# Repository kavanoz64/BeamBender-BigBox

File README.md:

# BeamBender BigBox

A digital scandoubler and HDMI output card for the **Amiga 4000**, with the **Amiga 2000 and 3000** supported as well.

The card plugs into the video slot, taps the digital RGB signals before they ever reach a DAC, and outputs clean **HDMI** with audio. No analog stage, no capture artifacts, no flicker.

> This project is a big-box adaptation of [**jbilander/BeamBender**](https://github.com/jbilander/BeamBender), Jörgen Bilander's scandoubler for the Amiga 1200 (and 500). The original design's approach and much of its analog and HDMI circuitry carry over directly. Jörgen has also provided hardware guidance throughout this redesign. All credit for the concept belongs upstream.

**Status: revision 0.3 works on the Amiga 4000D, 4000T, 3000 and 2000 (OCS, ECS and AGA): every Amiga screen mode including the A2024, DCTV and HAM-E pictures, motion-adaptive deinterlacing, integer and half-step scaling, and fourteen output formats from 640x480 to 1920x1200.** See [Status](#status).

**Using the card:** the [User Guide](USER_GUIDE.md) explains the on-screen menu and the three buttons. Loading the firmware is in [`Firmware/`](Firmware/README.md), the Amiga tools in [`BBLink/`](BBLink/README.md).

---

## What's different from the A1200 original

The A1200 version clips onto the Lisa chip and connects to the main board with an FFC cable. Big-box Amigas have the same signals on the video slot, so this version is a **single PCB with no cables**, taking digital RGB, syncs, the pixel clock, audio and power straight off the slot.

| | A1200 BeamBender | BeamBender BigBox |
|---|---|---|
| Signal source | Lisa chip (PLCC-84 clip) | Video slot |
| Boards | Two, joined by FFC | One |
| FPGA | Gowin GW1NR-9 (on-board) | Colorlight i5 or i9 module (SO-DIMM socket) |
| Video RAM | FPGA-internal | 8 MB 32-bit SDRAM on module |
| Audio in | 3.5 mm jack | Video slot, plus aux header and jack, mixed |
| Power | External connector | Slot |

---

## Hardware

**FPGA:** a [Colorlight i5 v7.0](https://github.com/wuxx/Colorlight-FPGA-Projects) module in a 200-pin DDR2 SO-DIMM socket (TE 1473149-4), with a Lattice **ECP5 LFE5U-25F** (24k LUT), **8 MB of 32-bit SDRAM** for the frame buffer, and its own configuration flash and regulators. The ECP5 only comes in BGA, so the module is deliberate: a dead one is a socket swap, not a rework job. **SO-DIMM pin 41**, the one ball that differs between the i5 and the i9, is left unconnected so the two are interchangeable.

**The i9 (LFE5U-45F, 44k LUT, 4 PLLs) is the recommended module** for the Rev 0.3 board. It drops into the same socket, and on a board without the clock generator below its two extra PLLs clock the seven formats that need 40, 65, 108 or 162 MHz. It is also the module with room for what comes next. Build with an i9 unless cost decides.

The **i5 (LFE5U-25F)** is the cheaper option, with its own bitstream. On its own it runs the other seven formats (640x480, 720x576 / 720x480, 1280x720, 1280x800, 1680x1050, 1920x1080 and 1920x1200), enough for most televisions and monitors; with the **Si5351C** fitted it runs all fourteen. It will be the recommended module for the Rev 0.4 and later boards.

**Clock generator:** an **Si5351C** makes the pixel clocks the ECP5's PLLs cannot make from 27 MHz: 162 MHz for 1600x1200, 108 for 1280x960, 1280x1024, 1440x900 and 1600x900, 65 for 1024x768 and 40 for 800x600. It is a rework on revision 0.3 and part of the next revision. One firmware per module serves boards with and without it: the card measures its clocks at power-up and offers only the formats it can make.

**Video out:** an **SiI9022A** HDMI transmitter, fed 24-bit RGB at up to 162 MHz. An ECP5 without SERDES cannot generate HDMI's TMDS signals itself fast enough for 1080p60.

**Audio:** an **AK5720** 24-bit ADC sends I²S straight to the SiI9022A. Ahead of it, an **OPA1692** summing amplifier mixes the Amiga's audio from the slot with an auxiliary input, on an internal header or a 3.5 mm jack (a plug in the jack disconnects the header), so another card's audio or an external source can be folded in.

**HDMI +5V:** a **TPS2553** load switch feeds HDMI pin 18, current-limited and blocking reverse current, so neither a shorted cable nor a television pushing 5V back can reach the Amiga's supply. The on-screen display reports its fault line.

**Level shifting:** two 74LVC16244 buffers translate the Amiga's 5V logic to 3.3V; the ECP5 is *not* 5V tolerant.

**Board:** 157.5 x 90 mm, 4-layer, with dedicated ground and 3V3 planes.

### Where to buy the module

[Colorlight i5 + ext-board bundle on AliExpress](https://www.aliexpress.us/item/3256807602160285.html)

Buy the **module and the dev board together**. The card programs the module in place through its JTAG header, but the dev board is a second, independent way to load or recover a bitstream.

---

## Clock architecture

| Clock | Source | ECP5 pin | PLL |
|---|---|---|---|
| **C28O**, 28.375 MHz PAL / 28.636 NTSC | Alice, via slot | 91 · `PCLKT2_1` | none, already the pixel clock |
| **VCDAC x2**, 14.19 MHz | Agnus/Alice CDAC, doubled on-board | 81 · `PCLKT3_1` | x2 to 28.375 MHz |
| **27 MHz** | on-board oscillator | 134 · `PCLKT7_1` | x5.5 to 148.5 MHz output |
| **24.576 MHz** | on-board oscillator | 89 · `PCLKT2_0` | none, audio MCLK reference |

**27 MHz** because 148.5 MHz, the pixel clock of 1080p at both 50 and 60 Hz, is exactly 27 x 5.5. The module's own 25 MHz cannot make it.

**The A2000 and A3000 have no 28 MHz clock on their video slots.** Their fastest, VCDAC at 7.09/7.16 MHz, is below the PLL's 8 MHz minimum, so an XOR gate and an RC delay double it on the board and the PLL takes it from there. The A4000 runs from C28O; the card detects which clock is present and picks it by itself.

---

## Amiga 2000 / 3000 support

The pre-AGA video slot carries **12-bit color** (RGB444), and each 4-bit value is widened to 8 bits exactly (0 to 0, 15 to 255). The card tells the machines apart by itself, from the AGA slot's extra pins, which only the A4000 has.

The A3000 and the A2000, with OCS and with ECS chips, are confirmed working.

---

## Programming

The module's JTAG pads are not on the SO-DIMM edge, so four **spring-loaded pogo pins** reach them from below, wired to a **1x6 JTAG header** on the card. An FT232H or FT2232H adapter and `openFPGALoader` write the firmware to the module's flash, from which the card boots on its own ([how](Firmware/README.md)).

---

## Firmware

The gateware captures the Amiga's digital RGB into the module's SDRAM, scales it and drives the SiI9022A.

**Prebuilt bitstreams are in [`Firmware/`](Firmware)**, two per module: the standard firmware and the `-c28` build, which locks 1920x1080 at 50 Hz to the Amiga's PAL frame ([which to load](Firmware/README.md#standard-or--c28)). The AmigaOS tools that drive the card are in [`BBLink/`](BBLink). The firmware **sources are not published yet**; they will be once the gateware is mature enough to hand to others.

**Output formats**, chosen from the menu:

| | i9 (recommended) | i5 | i5 with Si5351C |
|---|---|---|---|
| 640x480 | yes | yes | yes |
| 720x576 / 720x480 | yes | yes | yes |
| 800x600 | yes | no | yes |
| 1024x768 | yes | no | yes |
| 1280x720 | yes | yes | yes |
| 1280x800 | yes | yes | yes |
| 1280x960 | yes | no | yes |
| 1280x1024 | yes | no | yes |
| 1440x900 | yes | no | yes |
| 1600x900 | yes | no | yes |
| 1600x1200 | yes | no | yes |
| 1680x1050 | yes | yes | yes |
| 1920x1080 | yes | yes | yes |
| 1920x1200 | yes | yes | yes |

All of them run at 50 or 60 Hz, following the Amiga or forced from the menu. The 1280x800, 1440x900, 1600x900 and 1680x1050 formats drive panels of those sizes at their native resolution.

**Scaling.** The horizontal and vertical scales are set separately. **Auto** picks the largest whole scale that fits and centers the picture: PAL on 1080p is x2 by x3. Forced scales add **blended half steps**, x1.5 to x5.5, where the middle row or column of each pair is the average of the two, so the 288 lines of PAL overscan fill 1008 of 1080p's rows at x3.5 with no uneven scanlines. Super-Hires is drawn on its own 1280 samples, and LoRes screens are stored one sample per pixel, so a 320-pixel screen reaches x6. The menu counts in the screen's own pixels: a laced PAL screen is 640x512, a Super-Hires one 1280 wide.

**Overscan Auto** captures more of the Amiga's picture around the window you set, as much as fits at the scale in force, so a game or demo that draws into the overscan area is shown whole.

**Picture effects:** scanlines (Light, Medium, Deep), **Pixel Smoothing** (Soft, Softer, Softest: a sharp bilinear that takes the blockiness out of a scaled picture on a flat panel), and **Gamma**, 0.42 to 2.38 in eleven steps, which leaves black, white and the menu as they are.

**Input.** Every mode the Amiga's monitor drivers produce: PAL and NTSC, Euro36, Euro72, Super72, DblPAL, DblNTSC and Multiscan, in LoRes, HiRes and Super-Hires, progressive and interlaced. The card recognizes the mode by itself and keeps a settings set for each (separately for ECS and AGA), so the position and sampling phase you set for a mode come back with it. Interlaced screens are **deinterlaced motion-adaptively** on both modules: still parts are woven at full sharpness and only what moves is interpolated, so a still Workbench stays sharp and a moving pointer or window does not comb. Weave and Bob are there too, and Super-Hires interlace is woven.

**Custom monitors and the BB- drivers.** A monitor driver with timing of its own is taken as CUSTOM15 or CUSTOM24, by its line rate, with a settings set each. Four AmigaOS 3 monitor drivers of the card's own, in [`BBLink/Monitors`](BBLink/Monitors/README.md), make interlaced screens with the Amiga's own chipset, which the card weaves and shows 1:1 on the output format of the same size: a 1024x768 Workbench on a 1024x768 monitor, with no graphics card.

| Driver | Resolution | Colors on OCS | Colors on ECS | Colors on AGA |
|---|---|---|---|---|
| BB-800x600 | 800x600 | not supported | 16 (High Res) | 256 |
| BB-1024x768 | 1024x768 | not supported | 4 | 256 |
| BB-1280x1024 | 1280x1024 | not supported | 4 | 256 |
| BB-HD720p | 1280x720 | not supported | 4 | 256 |

They need AmigaOS 3.0 or later, and AGA or both ECS chips (an ECS Agnus and the ECS Denise). On ECS they have so far run in an emulator only.

**The A2024**, 15 Hz and 10 Hz, PAL and NTSC: the card reassembles the monitor's panels in its frame buffer, as the A2024 itself did, and shows the whole 1024x1024 (PAL) or 1024x800 (NTSC) grayscale picture 1:1 on 1280x1024 or 1080p. BeamBender BigBox is the first Amiga scandoubler to display the A2024 modes.

**DCTV and HAM-E.** The card decodes Digital Creations' **DCTV** and Black Belt Systems' **HAM-E** pictures itself, with neither box fitted, by reading the same digital lines the boxes read on the 23-pin video port. A picture is recognized by its DCTV signature or HAM-E cookie, so there is nothing to switch on; HAM-E works in both its register and HAM modes. The screen's first line has to be in the capture window or just above it (for HAM-E also its left edge), and DCTV widens the window by itself. Not on Super-Hires screens or A2024 monitors.

**On-screen display.** A text menu on the card's three buttons sets all of the above, with Display Info, Monitor Info, Monitor Modes and Si5351 Info pages. Settings are saved to the module's flash. Firmware from 2026-10-28.05 on does not read settings saved by older firmware, so back them up with BBLink before updating from one.

**Monitor Info** shows who the monitor is, from its EDID; **Monitor Modes** lists every output format and whether the monitor claims it at 50 and 60 Hz (one marked No may still work).

**Hot plug.** Replug the HDMI cable or swap the monitor, and the picture comes back on its own within about a second.

**Sampling calibration** finds the best capture phase against a still picture in about six seconds.

**The Amiga control link** is three wires between test points already on the card, a full-duplex link to AmigaOS. The tools in [`BBLink/`](BBLink) use it: `BBLink` (1.32) has every setting, the live pages and the card's buttons in a window, and backs the settings up to a text file and restores them; `BBKeyCon` puts the card's buttons on the keyboard; `BBSurvey`, `BBProbe`, `BBScreen` and `BBLag` measure and diagnose. The wiring is in that README.

**Latency**, measured with BBLag and a 240 fps camera: the HDMI picture is one to two fields (20 to 40 ms) behind an analog monitor's, the HDMI monitor's own processing included. One field of it is the frame buffer, by design.

---

## Status

**The revision 0.3 board works**, on an **Amiga 4000D**, an **Amiga 4000T**, an **Amiga 3000** and an **Amiga 2000**.

Confirmed on hardware:

- [x] HDMI output with audio, on several monitors
- [x] A4000D and A4000T (C28O), A3000 and A2000 (doubled VCDAC), OCS, ECS and AGA
- [x] Every screen mode: PAL, NTSC, DblPAL, DblNTSC, Super72, Euro36, Euro72 and Multiscan, Super-Hires at full width, interlace
- [x] The A2024, 15 Hz and 10 Hz, PAL and NTSC, as the full 1024-line picture
- [x] DCTV and HAM-E pictures, on both modules
- [x] Motion-adaptive deinterlacing, on both modules
- [x] Fourteen output formats, 640x480 to 1920x1200, at 50 and 60 Hz; all of them on the i5 with the Si5351C
- [x] Integer and blended half-step scaling, Overscan Auto, Pixel Smoothing, Gamma
- [x] The BB- monitor drivers, woven and shown 1:1
- [x] The on-screen menu, settings in flash, sampling calibration
- [x] Monitor Info and Monitor Modes from the monitor's EDID, hot plug
- [x] The Amiga control link and the BBLink tools
- [x] Latency: one to two fields to the HDMI monitor

Still open:

- [ ] Measure actual current on the 5V and 3.3V rails

### Next steps

**Hardware: revision 0.4**, in layout now:

- **An HDMI input for an RTG (ReTargetable Graphics) card** such as the Z3660, through an ADV7611 receiver: one monitor cable for the Amiga's screens and RTG, with the RTG card's audio. The menu, the status lines and Gamma work on the RTG picture too, with Gamma set for each source.
- **Automatic switching between the Amiga and RTG**, told by Aminet's `switchcontrol` over the parallel port, with the sound following the picture. The Amiga capture keeps running behind RTG, so switching back is instant.
- **The Si5351C on the board**, so every output format runs on both modules with no rework.
- **The Amiga control link on the board**, through the parallel port: no wires, and a byte per clock edge instead of a bit.
- **An RP2354B microcontroller** that runs the on-screen menu and everything shown over the picture, leaving room on the i5 for the RTG input. It also reads the Amiga keyboard, so the menu works from the keyboard, even in a game that boots from floppy.
- **The Gotek's FlashFloppy display on screen**, over either picture, so no display has to be fitted to the case.
- **USB-C on the back plate** for firmware updates from a PC, with no JTAG programmer. The card never draws power from USB.
- **A connector for optional Lisa and Denise tap boards** on the A4000 (Jörgen's [LISA_to_FPGA](https://github.com/jbilander/Lisa_to_FPGA)), on the A2000 and A3000 ([Denise_to_FPGA](https://github.com/jbilander/Denise_to_FPGA)) which pass Lisa and Denise's register writes to the FPGA.
- **The Amiga audio input chosen by a slide switch**: line or raw audio, for the A4000 or for the A2000 and A3000. No soldering, as for every user setting.
- Smaller changes: the audio master clock from its own oscillator, a 3A switching regulator for 3.3V, and right-angle JTAG and button headers.

**Firmware.** Publishing the sources.

---

## Building one

The revision 0.3 manufacturing files are in [`jlcpcb/`](jlcpcb), for **JLCPCB** fabrication and assembly. [`jlcpcb/production_files`](jlcpcb/production_files) holds the three files to upload there: the zipped Gerbers and drill files, the bill of materials with LCSC part numbers, and the pick-and-place file; [`jlcpcb/gerber`](jlcpcb/gerber) has the Gerbers unzipped. The Colorlight module and the pogo pins are fitted by hand afterwards. On this revision the Si5351C is a rework (without it the card offers the formats [above](#firmware) for its module), and the Amiga control link is three wires ([BBLink](BBLink/README.md)).

Fit an **i9** unless cost rules it out. A finished board needs no toolchain: load the matching bitstream from [`Firmware/`](Firmware).

---

## Credits

- **[Jörgen Bilander](https://github.com/jbilander)**, original BeamBender design, and ongoing guidance on this adaptation
- **[Salih Albayrak (aka Kavanoz)](https://github.com/kavanoz64)**, hardware design and implementation for BigBox
- **[Stefan Reinauer](https://github.com/reinauer)**, FPGA programming
- **Claude AI** (Anthropic), design review, component selection, gateware and documentation
- **[wuxx](https://github.com/wuxx/Colorlight-FPGA-Projects)** and the Colorlight reverse-engineering community, for module pinouts and documentation that the vendor doesn't publish

## License

Please check the licensing of the upstream [BeamBender](https://github.com/jbilander/BeamBender) project before redistributing derived work.

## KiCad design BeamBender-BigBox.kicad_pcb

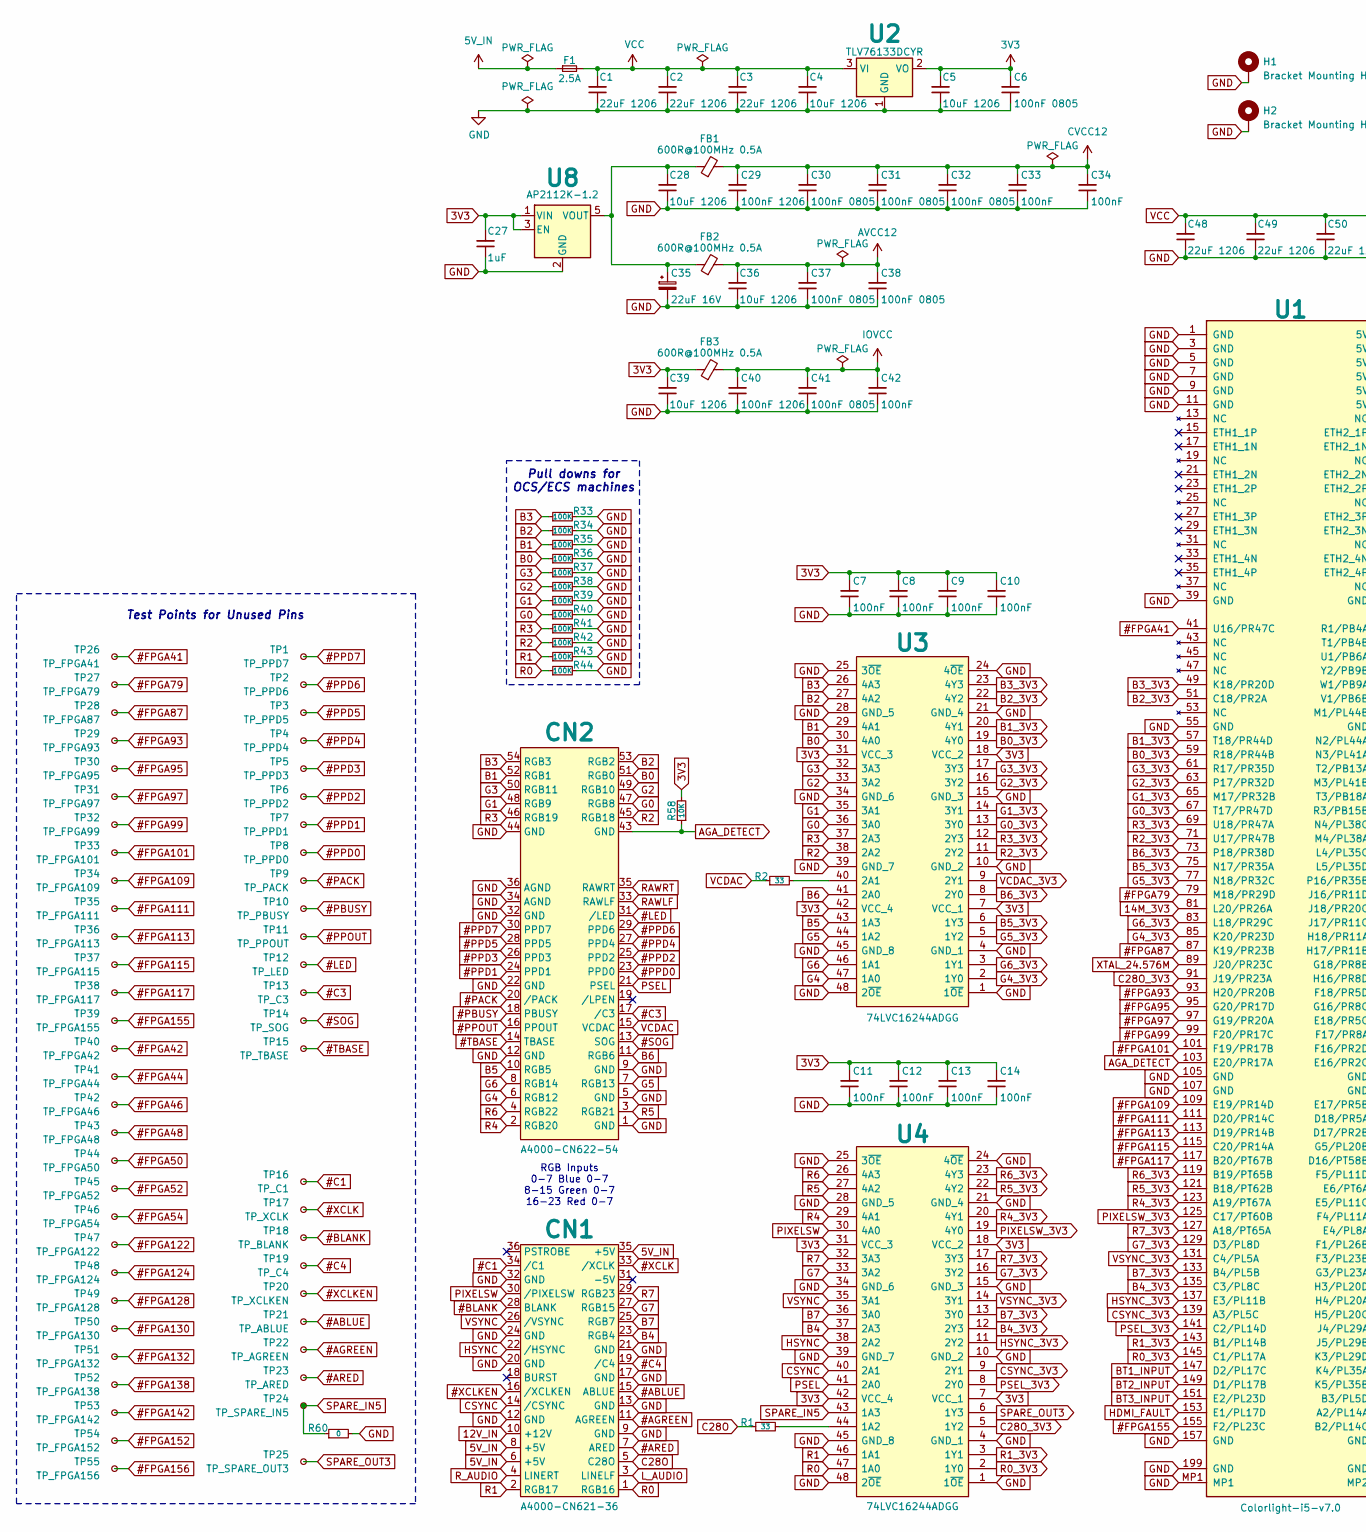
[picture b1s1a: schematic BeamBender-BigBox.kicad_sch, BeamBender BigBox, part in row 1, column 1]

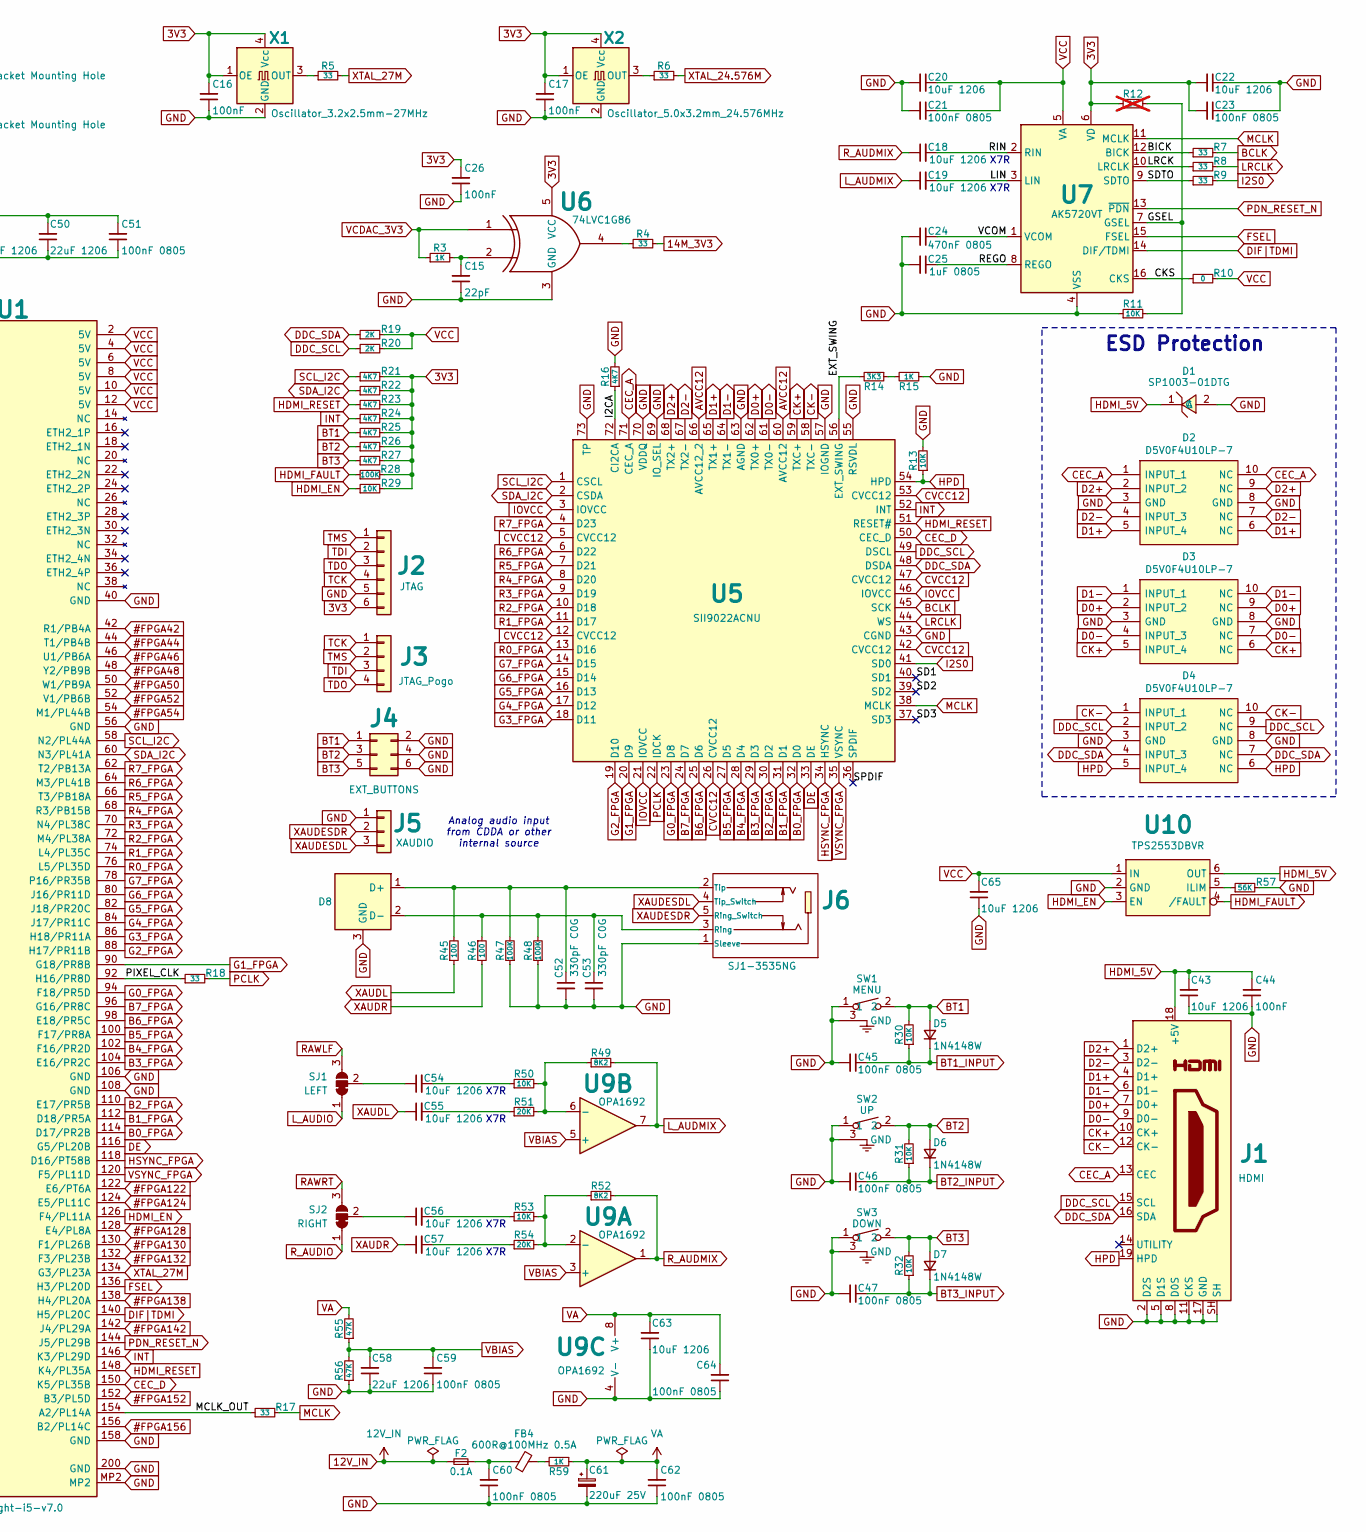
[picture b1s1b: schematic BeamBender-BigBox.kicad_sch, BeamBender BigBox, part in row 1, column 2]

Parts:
C1, C2, C3, C48, C49, C50, C58: 22uF 1206; C_1206_3216Metric; MPN CL31A226KOHNNNE; LCSC C90146
C4, C5, C18, C19, C20, C22, C28, C36, C39, C43, C54, C55, C56, C57, C63, C65: 10uF 1206; C_1206_3216Metric; MPN CL31B106KPHNNNE; LCSC C96449
C6, C21, C23, C30, C31, C32, C37, C38, C41, C45, C46, C47, C51, C59, C60, C62, C64: 100nF 0805; C_0805_2012Metric; MPN CL21B104KCFNNNE; LCSC C28233
C7, C8, C9, C10, C11, C12, C13, C14, C16, C17, C26, C33, C34, C42, C44: 100nF; C_0603_1608Metric; MPN CC0603KRX7R9BB104; LCSC C14663
C15: 22pF; C_0603_1608Metric; MPN CL10C220JB8NNNC; LCSC C1653
C24: 470nF 0805; C_0805_2012Metric; MPN CL21B474KBFNNNE; LCSC C13967
C25: 1uF 0805; C_0805_2012Metric; MPN CL21B105KBFNNNE; LCSC C28323
C27: 1uF; C_0603_1608Metric; MPN CL10A105KB8NNNC; LCSC C15849
C29, C40: 100nF 1206; C_1206_3216Metric; MPN CL31B104KBCNNNC; LCSC C24497
C35: 22uF 16V; CP_Elec_5x5.8; MPN UWT1C220MCL1GB; LCSC C445073
C52, C53: 330pF C0G; C_0603_1608Metric; MPN CL10C331JB8NNNC; LCSC C1664
C61: 220uF 25V; CP_Elec_6.3x7.7; MPN EEEFTE221XAP; LCSC C190724
CN1: A4000-CN621-36
CN2: A4000-CN622-54
D1: SP1003-01DTG; SOD-723_L1.0-W0.6-LS1.4-RD; MPN SP1003-01DTG; LCSC C126834
D2, D3, D4: D5V0F4U10LP-7; Diodes_UDFN-10_1.0x2.5mm_P0.5mm_HandSolder; MPN D5V0F4U10LP-7; LCSC C460833
D5, D6, D7: 1N4148W; D_SOD-123; MPN 1N4148W; LCSC C81598
D8: TPD2E009; SOT-23; MPN TPD2E009DBZR; LCSC C2871371
F1: 2.5A; Fuse_1206_3216Metric; MPN 1206L250/16AR; LCSC C42449089
F2: 0.1A; Fuse_1206_3216Metric; MPN JK-nSMD010/60V; LCSC C2830236
FB1, FB2, FB3, FB4: 600R@100MHz 0.5A; L_0805_2012Metric; MPN GZ2012D601TF; LCSC C1017
H1, H2: Bracket Mounting Hole; MountingHole_3.2mm_M3_Pad_Via
J1: HDMI; HDMI_A_Molex_208658-1001_Horizontal; MPN HDMI-001 19PCBTP; LCSC C138388
J2: JTAG; PinHeader_1x06_P2.54mm_Vertical; MPN HB-PH3-25416PB2GOP; LCSC C6332199
J3: JTAG_Pogo; PinHeader_1x04_P2.54mm_Pogo
J4: EXT_BUTTONS; PinHeader_2x03_P2.54mm_Vertical; MPN 2541WV-2x03P; LCSC C5383104
J5: XAUDIO; PinHeader_1x03_P2.54mm_Vertical; MPN 2541WV-03P; LCSC C5383112
J6: SJ1-3535NG; AUDIO-TH_SJ1-3535NG; MPN SJ1-3535NG; LCSC C4991610
R1, R2, R4, R5, R6, R7, R8, R9, R17, R18: 33; R_0603_1608Metric; MPN 0603WAF330JT5E; LCSC C23140
R3, R15, R59: 1K; R_0603_1608Metric; MPN 0603WAF1001T5E; LCSC C21190
R10, R60: 0; R_0603_1608Metric; MPN 0603WAF0000T5E; LCSC C21189
R11, R13, R29, R30, R31, R32, R50, R53, R58: 10K; R_0603_1608Metric; MPN 0603WAF1002T5E; LCSC C25804
R12: 1K; R_0603_1608Metric; MPN 0603WAF1001T5E; LCSC C21190; not fitted
R14: 3K3; R_0603_1608Metric; MPN 0603WAF3301T5E; LCSC C22978
R16, R21, R22, R23, R24, R25, R26, R27: 4K7; R_0603_1608Metric; MPN 0603WAF4701T5E; LCSC C23162
R19, R20: 2K; R_0603_1608Metric; MPN 0603WAF2001T5E; LCSC C22975
R28, R33, R34, R35, R36, R37, R38, R39, R40, R41, R42, R43, R44, R47, R48: 100K; R_0603_1608Metric; MPN 0603WAF1003T5E; LCSC C25803
R45, R46: 100; R_0603_1608Metric; MPN 0603WAF1000T5E; LCSC C22775
R49, R52: 8K2; R_0603_1608Metric; MPN 0603WAF8201T5E; LCSC C25981
R51, R54: 20K; R_0603_1608Metric; MPN 0603WAF2002T5E; LCSC C4184
R55, R56: 47K; R_0603_1608Metric; MPN 0603WAF4702T5E; LCSC C25819
R57: 56K; R_0603_1608Metric; MPN 0603WAF5602T5E; LCSC C23206
SJ1: LEFT; SolderJumper-3_P1.3mm_Bridged12_RoundedPad1.0x1.5mm
SJ2: RIGHT; SolderJumper-3_P1.3mm_Bridged12_RoundedPad1.0x1.5mm
SW1: MENU; KEY-TH_TS-1038-A10B3-D2; MPN TS-1038-A10B3-D2; LCSC C499341
SW2: UP; KEY-TH_TS-1038-A10B3-D2; MPN TS-1038-A10B3-D2; LCSC C499341
SW3: DOWN; KEY-TH_TS-1038-A10B3-D2; MPN TS-1038-A10B3-D2; LCSC C499341
TP1: TP_PPD7; TestPoint_Pad_D1.0mm
TP2: TP_PPD6; TestPoint_Pad_D1.0mm
TP3: TP_PPD5; TestPoint_Pad_D1.0mm
TP4: TP_PPD4; TestPoint_Pad_D1.0mm
TP5: TP_PPD3; TestPoint_Pad_D1.0mm
TP6: TP_PPD2; TestPoint_Pad_D1.0mm
TP7: TP_PPD1; TestPoint_Pad_D1.0mm
TP8: TP_PPD0; TestPoint_Pad_D1.0mm
TP9: TP_PACK; TestPoint_Pad_D1.0mm
TP10: TP_PBUSY; TestPoint_Pad_D1.0mm
TP11: TP_PPOUT; TestPoint_Pad_D1.0mm
TP12: TP_LED; TestPoint_Pad_D1.0mm
TP13: TP_C3; TestPoint_Pad_D1.0mm
TP14: TP_SOG; TestPoint_Pad_D1.0mm
TP15: TP_TBASE; TestPoint_Pad_D1.0mm
TP16: TP_C1; TestPoint_Pad_D1.0mm
TP17: TP_XCLK; TestPoint_Pad_D1.0mm
TP18: TP_BLANK; TestPoint_Pad_D1.0mm
TP19: TP_C4; TestPoint_Pad_D1.0mm
TP20: TP_XCLKEN; TestPoint_Pad_D1.0mm
TP21: TP_ABLUE; TestPoint_Pad_D1.0mm
TP22: TP_AGREEN; TestPoint_Pad_D1.0mm
TP23: TP_ARED; TestPoint_Pad_D1.0mm
TP24: TP_SPARE_IN5; TestPoint_Pad_D1.0mm
TP25: TP_SPARE_OUT3; TestPoint_Pad_D1.0mm
TP26: TP_FPGA41; TestPoint_Pad_D1.0mm
TP27: TP_FPGA79; TestPoint_Pad_D1.0mm
TP28: TP_FPGA87; TestPoint_Pad_D1.0mm
TP29: TP_FPGA93; TestPoint_Pad_D1.0mm
TP30: TP_FPGA95; TestPoint_Pad_D1.0mm
TP31: TP_FPGA97; TestPoint_Pad_D1.0mm
TP32: TP_FPGA99; TestPoint_Pad_D1.0mm
TP33: TP_FPGA101; TestPoint_Pad_D1.0mm
TP34: TP_FPGA109; TestPoint_Pad_D1.0mm
TP35: TP_FPGA111; TestPoint_Pad_D1.0mm
TP36: TP_FPGA113; TestPoint_Pad_D1.0mm
TP37: TP_FPGA115; TestPoint_Pad_D1.0mm
TP38: TP_FPGA117; TestPoint_Pad_D1.0mm
TP39: TP_FPGA155; TestPoint_Pad_D1.0mm
TP40: TP_FPGA42; TestPoint_Pad_D1.0mm
TP41: TP_FPGA44; TestPoint_Pad_D1.0mm
TP42: TP_FPGA46; TestPoint_Pad_D1.0mm
TP43: TP_FPGA48; TestPoint_Pad_D1.0mm
TP44: TP_FPGA50; TestPoint_Pad_D1.0mm
TP45: TP_FPGA52; TestPoint_Pad_D1.0mm
TP46: TP_FPGA54; TestPoint_Pad_D1.0mm
TP47: TP_FPGA122; TestPoint_Pad_D1.0mm
TP48: TP_FPGA124; TestPoint_Pad_D1.0mm
TP49: TP_FPGA128; TestPoint_Pad_D1.0mm
TP50: TP_FPGA130; TestPoint_Pad_D1.0mm
TP51: TP_FPGA132; TestPoint_Pad_D1.0mm
TP52: TP_FPGA138; TestPoint_Pad_D1.0mm
TP53: TP_FPGA142; TestPoint_Pad_D1.0mm
TP54: TP_FPGA152; TestPoint_Pad_D1.0mm
TP55: TP_FPGA156; TestPoint_Pad_D1.0mm
U1: Colorlight-i5-v7.0; 1473149-4; MPN 1473149-4; LCSC C591654
U2: TLV76133DCYR; SOT-223-3_TabPin2; MPN TLV76133DCYR; LCSC C7527500
U3, U4: 74LVC16244ADGG; TSSOP-48_6.1x12.5mm_P0.5mm; MPN 74LVC16244ADGG,118; LCSC C6070
U5: SII9022ACNU; QFN-72-1EP_10x10mm_P0.5mm_EP6x6mm_ThermalVias_HandSolder; MPN SII9022ACNU; LCSC C369565
U6: 74LVC1G86; SOT-23-5; MPN SN74LVC1G86DBVR; LCSC C402161
U7: AK5720VT; TSSOP-16_4.4x5mm_P0.65mm; MPN AK5720VT; LCSC C1519002
U8: AP2112K-1.2; SOT-23-5; MPN AP2112K-1.2TRG1; LCSC C460310
U9: OPA1692; SOIC-8_3.9x4.9mm_P1.27mm; MPN OPA1692IDR; LCSC C2060550
U10: TPS2553DBVR; SOT-23-6; MPN TPS2553DBVR; LCSC C55266
X1: Oscillator_3.2x2.5mm-27MHz; Crystal_SMD_3225-4Pin_3.2x2.5mm; MPN XOS32027000LT00351005; LCSC C37635418
X2: Oscillator_5.0x3.2mm_24.576MHz; Oscillator_SMD_EuroQuartz_XO53-4Pin_5.0x3.2mm; MPN SX5M24.576M20F30TNN; LCSC C2901534

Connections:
3V3: C5.2, C6.2, C7.2, C8.2, C9.2, C10.2, C11.2, C12.2, C13.2, C14.2, C16.2, C17.2, C22.2, C23.2, C26.2, C27.2, C39.2, FB3.1, J2.6, R12.1, R21.2, R22.2, R23.2, R24.2, R25.2, R26.2, R27.2, R28.2, R29.2, R58.2, U2.2 (VO), U3.7 (VCC_1), U3.18 (VCC_2), U3.31 (VCC_3), U3.42 (VCC_4), U4.7 (VCC_1), U4.18 (VCC_2), U4.31 (VCC_3), U4.42 (VCC_4), U6.5 (VCC), U7.6 (VD), U8.1 (VIN), U8.3 (EN), X1.1 (OE), X1.4 (Vcc), X2.1 (OE), X2.4 (Vcc)
5V_IN: CN1.6 (+5V), CN1.8 (+5V), CN1.35 (+5V), F1.1
12V_IN: CN1.10 (+12V), F2.2
14M_3V3: R4.2, U1.81 (L20/PR26A)
#ABLUE: CN1.15 (ABLUE), TP21.1 (1_1)
#AGREEN: CN1.11 (AGREEN), TP22.1 (1_1)
#ARED: CN1.7 (ARED), TP23.1 (1_1)
#BLANK: CN1.28 (BLANK), TP18.1 (1_1)
#C1: CN1.34 (/C1), TP16.1 (1_1)
#C3: CN2.17 (/C3), TP13.1 (1_1)
#C4: CN1.19 (/C4), TP19.1 (1_1)
#FPGA41: TP26.1 (1_1), U1.41 (U16/PR47C)
#FPGA42: TP40.1 (1_1), U1.42 (R1/PB4A)
#FPGA44: TP41.1 (1_1), U1.44 (T1/PB4B)
#FPGA46: TP42.1 (1_1), U1.46 (U1/PB6A)
#FPGA48: TP43.1 (1_1), U1.48 (Y2/PB9B)
#FPGA50: TP44.1 (1_1), U1.50 (W1/PB9A)
#FPGA52: TP45.1 (1_1), U1.52 (V1/PB6B)
#FPGA54: TP46.1 (1_1), U1.54 (M1/PL44B)
#FPGA79: TP27.1 (1_1), U1.79 (M18/PR29D)
#FPGA87: TP28.1 (1_1), U1.87 (K19/PR23B)
#FPGA93: TP29.1 (1_1), U1.93 (H20/PR20B)
#FPGA95: TP30.1 (1_1), U1.95 (G20/PR17D)
#FPGA97: TP31.1 (1_1), U1.97 (G19/PR20A)
#FPGA99: TP32.1 (1_1), U1.99 (F20/PR17C)
#FPGA101: TP33.1 (1_1), U1.101 (F19/PR17B)
#FPGA109: TP34.1 (1_1), U1.109 (E19/PR14D)
#FPGA111: TP35.1 (1_1), U1.111 (D20/PR14C)
#FPGA113: TP36.1 (1_1), U1.113 (D19/PR14B)
#FPGA115: TP37.1 (1_1), U1.115 (C20/PR14A)
#FPGA117: TP38.1 (1_1), U1.117 (B20/PT67B)
#FPGA122: TP47.1 (1_1), U1.122 (E6/PT6A)
#FPGA124: TP48.1 (1_1), U1.124 (E5/PL11C)
#FPGA128: TP49.1 (1_1), U1.128 (E4/PL8A)
#FPGA130: TP50.1 (1_1), U1.130 (F1/PL26B)
#FPGA132: TP51.1 (1_1), U1.132 (F3/PL23B)
#FPGA138: TP52.1 (1_1), U1.138 (H4/PL20A)
#FPGA142: TP53.1 (1_1), U1.142 (J4/PL29A)
#FPGA152: TP54.1 (1_1), U1.152 (B3/PL5D)
#FPGA155: TP39.1 (1_1), U1.155 (F2/PL23C)
#FPGA156: TP55.1 (1_1), U1.156 (B2/PL14C)
#LED: CN2.31 (/LED), TP12.1 (1_1)
#PACK: CN2.20 (/PACK), TP9.1 (1_1)
#PBUSY: CN2.18 (PBUSY), TP10.1 (1_1)
#PPD0: CN2.23 (PPD0), TP8.1 (1_1)
#PPD1: CN2.24 (PPD1), TP7.1 (1_1)
#PPD2: CN2.25 (PPD2), TP6.1 (1_1)
#PPD3: CN2.26 (PPD3), TP5.1 (1_1)
#PPD4: CN2.27 (PPD4), TP4.1 (1_1)
#PPD5: CN2.28 (PPD5), TP3.1 (1_1)
#PPD6: CN2.29 (PPD6), TP2.1 (1_1)
#PPD7: CN2.30 (PPD7), TP1.1 (1_1)
#PPOUT: CN2.16 (PPOUT), TP11.1 (1_1)
#SOG: CN2.13 (SOG), TP14.1 (1_1)
#TBASE: CN2.14 (TBASE), TP15.1 (1_1)
#XCLK: CN1.33 (/XCLK), TP17.1 (1_1)
#XCLKEN: CN1.16 (/XCLKEN), TP20.1 (1_1)
/BICK: R7.1, U7.12 (BICK)
/CKS: R10.1, U7.16 (CKS)
/EXT_SWING: R14.2, U5.56 (EXT_SWING)
/GSEL: R11.2, R12.2, U7.7 (GSEL)
/I2CA: R16.1, U5.72 (CI2CA)
/LIN: C19.2, U7.3 (LIN)
/LRCK: R8.1, U7.10 (LRCLK)
/MCLK_OUT: R17.1, U1.154 (A2/PL14A)
/PIXEL_CLK: R18.1, U1.92 (H16/PR8D)
/REGO: C25.1, U7.8 (REGO)
/RIN: C18.2, U7.2 (RIN)
/SD1: U5.40 (SD1)
/SD2: U5.39 (SD2)
/SD3: U5.37 (SD3)
/SDTO: R9.1, U7.9 (SDTO)
/SPDIF: U5.36 (SPDIF)
/VCOM: C24.1, U7.1 (VCOM)
AGA_DETECT: CN2.43 (GND), R58.1, U1.103 (E20/PR17A)
AVCC12: C36.2, C37.2, C38.2, FB2.2, U5.60 (AVCC12), U5.66 (AVCC12_2)
B0: CN2.51 (RGB0), R36.1, U3.30 (4A0)
B0_3V3: U1.59 (R18/PR44B), U3.19 (4Y0)
B0_FPGA: U1.114 (D17/PR2B), U5.32 (D0)
B1: CN2.52 (RGB1), R35.1, U3.29 (4A1)
B1_3V3: U1.57 (T18/PR44D), U3.20 (4Y1)
B1_FPGA: U1.112 (D18/PR5A), U5.31 (D1)
B2: CN2.53 (RGB2), R34.1, U3.27 (4A2)
B2_3V3: U1.51 (C18/PR2A), U3.22 (4Y2)
B2_FPGA: U1.110 (E17/PR5B), U5.30 (D2)
B3: CN2.54 (RGB3), R33.1, U3.26 (4A3)
B3_3V3: U1.49 (K18/PR20D), U3.23 (4Y3)
B3_FPGA: U1.104 (E16/PR2C), U5.29 (D3)
B4: CN1.23 (RGB4), U4.37 (2A3)
B4_3V3: U1.135 (C3/PL8C), U4.12 (2Y3)
B4_FPGA: U1.102 (F16/PR2D), U5.28 (D4)
B5: CN2.10 (RGB5), U3.43 (1A3)
B5_3V3: U1.75 (N17/PR35A), U3.6 (1Y3)
B5_FPGA: U1.100 (F17/PR8A), U5.27 (D5)
B6: CN2.11 (RGB6), U3.41 (2A0)
B6_3V3: U1.73 (P18/PR38D), U3.8 (2Y0)
B6_FPGA: U1.98 (E18/PR5C), U5.25 (D6)
B7: CN1.25 (RGB7), U4.36 (3A0)
B7_3V3: U1.133 (B4/PL5B), U4.13 (3Y0)
B7_FPGA: U1.96 (G16/PR8C), U5.24 (D7)
BCLK: R7.2, U5.45 (SCK)
BT1: D5.2 (A), J4.1, R25.1, R30.2, SW1.2
BT1_INPUT: C45.1, D5.1 (K), R30.1, U1.147 (D2/PL17C)
BT2: D6.2 (A), J4.3, R26.1, R31.2, SW2.2
BT2_INPUT: C46.1, D6.1 (K), R31.1, U1.149 (D1/PL17B)
BT3: D7.2 (A), J4.5, R27.1, R32.2, SW3.2
BT3_INPUT: C47.1, D7.1 (K), R32.1, U1.151 (E2/PL23D)
C28O: CN1.5 (C28O), R1.1
C28O_3V3: U1.91 (J19/PR23A), U4.5 (1Y2)
CEC_A: D2.1 (INPUT_1), D2.10 (NC), J1.13 (CEC), U5.71 (CEC_A)
CEC_D: U1.150 (K5/PL35B), U5.50 (CEC_D)
CK+: D3.5 (INPUT_4), D3.6 (NC), J1.10 (CK+), U5.59 (TXC+)
CK-: D4.1 (INPUT_1), D4.10 (NC), J1.12 (CK-), U5.58 (TXC-)
CSYNC: CN1.14 (/CSYNC), U4.40 (2A1)
CSYNC_3V3: U1.139 (A3/PL5C), U4.9 (2Y1)
CVCC12: C29.2, C30.2, C31.2, C32.2, C33.2, C34.2, FB1.2, U5.5 (CVCC12), U5.12 (CVCC12), U5.26 (CVCC12), U5.42 (CVCC12), U5.47 (CVCC12), U5.53 (CVCC12)
D0+: D3.2 (INPUT_2), D3.9 (NC), J1.7 (D0+), U5.62 (TX0+)
D0-: D3.4 (INPUT_3), D3.7 (NC), J1.9 (D0-), U5.61 (TX0-)
D1+: D2.5 (INPUT_4), D2.6 (NC), J1.4 (D1+), U5.65 (TX1+)
D1-: D3.1 (INPUT_1), D3.10 (NC), J1.6 (D1-), U5.64 (TX1-)
D2+: D2.2 (INPUT_2), D2.9 (NC), J1.1 (D2+), U5.68 (TX2+)
D2-: D2.4 (INPUT_3), D2.7 (NC), J1.3 (D2-), U5.67 (TX2-)
DDC_SCL: D4.2 (INPUT_2), D4.9 (NC), J1.15 (SCL), R20.1, U5.49 (DSCL)
DDC_SDA: D4.4 (INPUT_3), D4.7 (NC), J1.16 (SDA), R19.1, U5.48 (DSDA)
DE: U1.116 (G5/PL20B), U5.33 (DE)
DIF|TDMI: U1.140 (H5/PL20C), U7.14 (DIF/TDMI)
FSEL: U1.136 (H3/PL20D), U7.15 (FSEL)
G0: CN2.47 (RGB8), R40.1, U3.36 (3A0)
G0_3V3: U1.67 (T17/PR47D), U3.13 (3Y0)
G0_FPGA: U1.94 (F18/PR5D), U5.23 (D8)
G1: CN2.48 (RGB9), R39.1, U3.35 (3A1)
G1_3V3: U1.65 (M17/PR32B), U3.14 (3Y1)
G1_FPGA: U1.90 (G18/PR8B), U5.20 (D9)
G2: CN2.49 (RGB10), R38.1, U3.33 (3A2)
G2_3V3: U1.63 (P17/PR32D), U3.16 (3Y2)
G2_FPGA: U1.88 (H17/PR11B), U5.19 (D10)
G3: CN2.50 (RGB11), R37.1, U3.32 (3A3)
G3_3V3: U1.61 (R17/PR35D), U3.17 (3Y3)
G3_FPGA: U1.86 (H18/PR11A), U5.18 (D11)
G4: CN2.6 (RGB12), U3.47 (1A0)
G4_3V3: U1.85 (K20/PR23D), U3.2 (1Y0)
G4_FPGA: U1.84 (J17/PR11C), U5.17 (D12)
G5: CN2.7 (RGB13), U3.44 (1A2)
G5_3V3: U1.77 (N18/PR32C), U3.5 (1Y2)
G5_FPGA: U1.82 (J18/PR20C), U5.16 (D13)
G6: CN2.8 (RGB14), U3.46 (1A1)
G6_3V3: U1.83 (L18/PR29C), U3.3 (1Y1)
G6_FPGA: U1.80 (J16/PR11D), U5.15 (D14)
G7: CN1.27 (RGB15), U4.33 (3A2)
G7_3V3: U1.129 (D3/PL8D), U4.16 (3Y2)
G7_FPGA: U1.78 (P16/PR35B), U5.14 (D15)
GND: C1.1, C2.1, C3.1, C4.1, C5.1, C6.1, C7.1, C8.1, C9.1, C10.1, C11.1, C12.1, C13.1, C14.1, C15.1, C16.1, C17.1, C20.2, C21.2, C22.1, C23.1, C24.2, C25.2, C26.1, C27.1, C28.1, C29.1, C30.1, C31.1, C32.1, C33.1, C34.1, C35.2, C36.1, C37.1, C38.1, C39.1, C40.1, C41.1, C42.1, C43.1, C44.1, C45.2, C46.2, C47.2, C48.1, C49.1, C50.1, C51.1, C52.2, C53.2, C58.1, C59.1, C60.1, C61.2, C62.1, C63.1, C64.1, C65.1, CN1.9 (GND), CN1.12 (GND), CN1.13 (GND), CN1.17 (GND), CN1.20 (GND), CN1.21 (GND), CN1.24 (GND), CN1.32 (GND), CN2.1 (GND), CN2.5 (GND), CN2.9 (GND), CN2.12 (GND), CN2.22 (GND), CN2.32 (GND), CN2.34 (AGND), CN2.36 (AGND), CN2.44 (GND), D1.2 (A), D2.3 (GND), D2.8 (GND), D3.3 (GND), D3.8 (GND), D4.3 (GND), D4.8 (GND), D8.3 (GND), H1.1 (1_1), H2.1 (1_1), J1.2 (D2S), J1.5 (D1S), J1.8 (D0S), J1.11 (CKS), J1.17 (GND), J1.SH, J2.5, J4.2, J4.4, J4.6, J5.1, J6.1 (Sleeve), R11.1, R13.2, R15.1, R16.2, R33.2, R34.2, R35.2, R36.2, R37.2, R38.2, R39.2, R40.2, R41.2, R42.2, R43.2, R44.2, R47.1, R48.1, R56.1, R57.2, R60.2, SW1.1, SW1.3 (GND), SW2.1, SW2.3 (GND), SW3.1, SW3.3 (GND), U1.1 (GND), U1.3 (GND), U1.5 (GND), U1.7 (GND), U1.9 (GND), U1.11 (GND), U1.39 (GND), U1.40 (GND), U1.55 (GND), U1.56 (GND), U1.105 (GND), U1.106 (GND), U1.107 (GND), U1.108 (GND), U1.157 (GND), U1.158 (GND), U1.199 (GND), U1.200 (GND), U1.MP1, U1.MP2, U2.1 (GND), U3.1 (1~OE), U3.4 (GND_1), U3.10 (GND_2), U3.15 (GND_3), U3.21 (GND_4), U3.24 (4~OE), U3.25 (3~OE), U3.28 (GND_5), U3.34 (GND_6), U3.39 (GND_7), U3.45 (GND_8), U3.48 (2~OE), U4.1 (1~OE), U4.4 (GND_1), U4.10 (GND_2), U4.15 (GND_3), U4.21 (GND_4), U4.24 (4~OE), U4.25 (3~OE), U4.28 (GND_5), U4.34 (GND_6), U4.39 (GND_7), U4.45 (GND_8), U4.48 (2~OE), U5.43 (CGND), U5.55 (RSVDL), U5.57 (IOGND), U5.63 (AGND), U5.69 (IO_SEL), U5.70 (VDDQ), U5.73 (TP), U6.3 (GND), U7.4 (VSS), U8.2 (GND), U9.4 (V-), U10.2 (GND), X1.2 (GND), X2.2 (GND)
HDMI_5V: C43.2, C44.2, D1.1 (C), J1.18 (+5V), U10.6 (OUT)
HDMI_EN: R29.1, U1.126 (F4/PL11A), U10.3 (EN)
HDMI_FAULT: R28.1, U1.153 (E1/PL17D), U10.4 (/FAULT)
HDMI_RESET: R23.1, U1.148 (K4/PL35A), U5.51 (RESET#)
HPD: D4.5 (INPUT_4), D4.6 (NC), J1.19 (HPD), R13.1, U5.54 (HPD)
HSYNC: CN1.22 (/HSYNC), U4.38 (2A2)
HSYNC_3V3: U1.137 (E3/PL11B), U4.11 (2Y2)
HSYNC_FPGA: U1.118 (D16/PT58B), U5.34 (HSYNC)
I2S0: R9.2, U5.41 (SD0)
INT: R24.1, U1.146 (K3/PL29D), U5.52 (INT)
IOVCC: C40.2, C41.2, C42.2, FB3.2, U5.3 (IOVCC), U5.21 (IOVCC), U5.46 (IOVCC)
LRCLK: R8.2, U5.44 (WS)
L_AUDIO: CN1.3 (LINELF), SJ1.1 (A)
L_AUDMIX: C19.1, R49.2, U9.7
MCLK: R17.2, U5.38 (MCLK), U7.11 (MCLK)
unnamed: C15.2, R3.2, U6.2
unnamed: C54.2, R50.1
unnamed: C55.2, R51.1
unnamed: C56.2, R53.1
unnamed: C57.2, R54.1
unnamed: C60.2, F2.1, FB4.1
unnamed: C52.1, D8.1 (D+), J6.2 (Tip), R45.2, R47.2
unnamed: C53.1, D8.2 (D-), J6.3 (Ring), R46.1, R48.2
unnamed: FB4.2, R59.2
unnamed: R4.1, U6.4
unnamed: R14.1, R15.2
unnamed: C54.1, SJ1.2 (C)
unnamed: C56.1, SJ2.2 (C)
unnamed: R2.2, U3.40 (2A1)
unnamed: R1.2, U4.44 (1A2)
unnamed: C28.2, C35.1, FB1.1, FB2.1, U8.5 (VOUT)
unnamed: R52.1, R53.2, R54.2, U9.2 (-)
unnamed: R49.1, R50.2, R51.2, U9.6 (-)
unnamed: R57.1, U10.5 (ILIM)
unnamed: R5.1, X1.3 (OUT)
unnamed: R6.1, X2.3 (OUT)
PCLK: R18.2, U5.22 (IDCK)
PDN_RESET_N: U1.144 (J5/PL29B), U7.13 (~PDN)
PIXELSW: CN1.30 (/PIXELSW), U4.30 (4A0)
PIXELSW_3V3: U1.125 (C17/PT60B), U4.19 (4Y0)
PSEL: CN2.21 (PSEL), U4.41 (2A0)
PSEL_3V3: U1.141 (C2/PL14D), U4.8 (2Y0)
R0: CN1.1 (RGB16), R44.1, U4.47 (1A0)
R0_3V3: U1.145 (C1/PL17A), U4.2 (1Y0)
R0_FPGA: U1.76 (L5/PL35D), U5.13 (D16)
R1: CN1.2 (RGB17), R43.1, U4.46 (1A1)
R1_3V3: U1.143 (B1/PL14B), U4.3 (1Y1)
R1_FPGA: U1.74 (L4/PL35C), U5.11 (D17)
R2: CN2.45 (RGB18), R42.1, U3.38 (2A2)
R2_3V3: U1.71 (U17/PR47B), U3.11 (2Y2)
R2_FPGA: U1.72 (M4/PL38A), U5.10 (D18)
R3: CN2.46 (RGB19), R41.1, U3.37 (2A3)
R3_3V3: U1.69 (U18/PR47A), U3.12 (2Y3)
R3_FPGA: U1.70 (N4/PL38C), U5.9 (D19)
R4: CN2.2 (RGB20), U4.29 (4A1)
R4_3V3: U1.123 (A19/PT67A), U4.20 (4Y1)
R4_FPGA: U1.68 (R3/PB15B), U5.8 (D20)
R5: CN2.3 (RGB21), U4.27 (4A2)
R5_3V3: U1.121 (B18/PT62B), U4.22 (4Y2)
R5_FPGA: U1.66 (T3/PB18A), U5.7 (D21)
R6: CN2.4 (RGB22), U4.26 (4A3)
R6_3V3: U1.119 (B19/PT65B), U4.23 (4Y3)
R6_FPGA: U1.64 (M3/PL41B), U5.6 (D22)
R7: CN1.29 (RGB23), U4.32 (3A3)
R7_3V3: U1.127 (A18/PT65A), U4.17 (3Y3)
R7_FPGA: U1.62 (T2/PB13A), U5.4 (D23)
RAWLF: CN2.33 (RAWLF), SJ1.3 (B)
RAWRT: CN2.35 (RAWRT), SJ2.3 (B)
R_AUDIO: CN1.4 (LINERT), SJ2.1 (A)
R_AUDMIX: C18.1, R52.2, U9.1
SCL_I2C: R21.1, U1.58 (N2/PL44A), U5.1 (CSCL)
SDA_I2C: R22.1, U1.60 (N3/PL41A), U5.2 (CSDA)
SPARE_IN5: R60.1, TP24.1 (1_1), U4.43 (1A3)
SPARE_OUT3: TP25.1 (1_1), U4.6 (1Y3)
TCK: J2.4, J3.1
TDI: J2.2, J3.3
TDO: J2.3, J3.4
TMS: J2.1, J3.2
VA: C61.1, C62.2, C63.2, C64.2, R55.2, R59.1, U9.8 (V+)
VBIAS: C58.2, C59.2, R55.1, R56.2, U9.3 (+), U9.5 (+)
VCC: C1.2, C2.2, C3.2, C4.2, C20.1, C21.1, C48.2, C49.2, C50.2, C51.2, C65.2, F1.2, R10.2, R19.2, R20.2, U1.2 (5V), U1.4 (5V), U1.6 (5V), U1.8 (5V), U1.10 (5V), U1.12 (5V), U2.3 (VI), U7.5 (VA), U10.1 (IN)
VCDAC: CN2.15 (VCDAC), R2.1
VCDAC_3V3: R3.1, U3.9 (2Y1), U6.1
VSYNC: CN1.26 (/VSYNC), U4.35 (3A1)
VSYNC_3V3: U1.131 (C4/PL5A), U4.14 (3Y1)
VSYNC_FPGA: U1.120 (F5/PL11D), U5.35 (VSYNC)
XAUDESDL: J5.3, J6.4 (Tip_Switch)
XAUDESDR: J5.2, J6.5 (Ring_Switch)
XAUDL: C55.1, R45.1
XAUDR: C57.1, R46.2
XTAL_24.576M: R6.2, U1.89 (J20/PR23C)
XTAL_27M: R5.2, U1.134 (G3/PL23A)

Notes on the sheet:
X7R
ESD Protection
Analog audio input from CDDA or other internal source
Test Points for Unused Pins
RGB Inputs 0-7 Blue 0-7 8-15 Green 0-7 16-23 Red 0-7
Pull downs for OCS/ECS machines

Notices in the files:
BeamBender-BigBox.kicad_pcb:
Design by J.Bilander, S.Reinauer, S.Albayrak (C) 2026
